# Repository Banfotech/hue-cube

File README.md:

# Introduction 

The HueCube is a small colorful, programmable cube measuring 46x46x46mm.
You can play around with the example code using the [Arduino IDE](https://www.arduino.cc/), and change it's behavior.
By reading data from the embedded sensors, you can let the colors change by temperature, height, angle, tapping, tilting, dropping or humidity. See the following videos for a few examples:

## What do you need?

### Soldering
To assemble the board you need to be able to solder SMD components (0603) and a few pins. I am using [this](https://www.aliexpress.com/item/Hot-Sale-220V-110V-60W-Adjustable-Temperature-Electric-Soldering-Iron-Welding-Solder-Station-Heat-Pencil-With/32434361333.html) and [this](https://www.aliexpress.com/item/Free-Shipping-0-3mm-0-4mm-0-5-mm0-6mm-Tin-Lead-Rosin-Core-Solder-Wire/32335236726.html).

### Software
- [Blender3D](https://www.blender.org/), to design the 3d printed case:
    * USB Powered: <br/>
    * LiPo Powered:<br/>
- [KiCad](http://kicad-pcb.org/), to design the PCB
    * Schematics: <br/>
    * Circuit Board: <br/>
- [Arduino IDE](https://www.arduino.cc/), to write the code and flash the device
   * <br/>
   * The [light_ws2812](https://github.com/cpldcpu/light_ws2812) library to control the LEDs. Download the .zip from the `/light_ws2812_Arduino/` folder and place it into `Arduino/libraries/`. I chose this library, due to the small flash size of the attiny85.

### Hardware
The HueCube is made of small, electronic modules that are soldered onto a PCB. You can order the PCB directly from [AISLER](https://aisler.net/p/VAADXKWB), or use the [KiCad](http://kicad-pcb.org/) project files form this repository to modify it.
Currently, there are two design variant.

- USB Powered
    * 3D printed parts: 1x `BlenderModel/hc-v3-usb-base.stl` and  1x `BlenderModel/hc-v3-usb-cube.stl`
    * [1x ATTiny / DigiSpark](https://www.aliexpress.com/item/Attiny85-Digispark-Kickstarter-Development-Board-Module-For-Arduino-Built-in-USB-500ma-5V-Regulator-8k-Flash/32279051124.html)
    * [1x MPU-6050](https://www.aliexpress.com/item/MPU-6050-3-Axis-gyroscope-acce-lerometer-module-3V-5V-compatible-For-Arduino/2035920870.html)
    * [1x ON/OFF Switch](https://www.aliexpress.com/item/Promotion-50-Pcs-SS12D00G3-2-Position-SPDT-1P2T-3-Pin-PCB-Panel-Mini-Vertical-Slide-Switch/32649542037.html) (I know, not the ideal switch, but I had those lying around, so I will be using them)
    * [3x WS2812B](https://www.aliexpress.com/item/100PCS-New-Version-WS2812B-5050-RGB-SMD-WS2811-IC-WS2812-For-Strip-Screen-etc/32776703442.html) you can use them for all sorts of projects ;)
    * [3x 0603 100nF Capacitor](https://www.aliexpress.com/item/MCIGICM-100pcs-0603-smd-capacitor-ceramic-22pf-100nf-1uf-2-2uf-4-7uf-10uf-capacitors-kit/32841971485.html) (or you could search for a kit with multiple values)
- LiPo Powered
    * 3D printer files: 1x `BlenderModel/hc-v3-lipo-base.stl` and 1x `BlenderModel/hc-v3-lipo-cube.stl`
    * [1x TP4056 LiPo Charger](https://www.aliexpress.com/item/5Pcs-Lot-TP4056-Micro-USB-5V-1A-18650-Lithium-Battery-Charger-Board-With-Led-Indicator-Over/32675099957.html) **⚠️make sure to replace the PROG resistor⚠️**. The resistor value depends on your LiPo size. When using a 400mA battery, use [1x 10k Ohm 0603](https://www.aliexpress.com/item/300pcs-0603-SMD-Resistor-1-6-8K-7-5K-8-2K-9-1K-10K-ohm/32308220603.html?spm=a2g0s.9042311.0.0.27424c4dsotU5N), this will give you around ~100mA charging current. (or you could search for a kit with multiple values)
    * [1x MT3608 DC-DC Step Up Converter](https://www.aliexpress.com/item/5pcs-MT3608-DC-DC-Step-Up-Power-Apply-Module-Booster-Power-Module-MAX-output-28V-2A/32517710689.html) **⚠️set this to 5V output before soldering⚠️**

## How to Build?

### Soldering

#### Manually soldering the LEDs
First, solder the WS2812B to the PCB, note the corner with the triangle is GND, so this needs to be aligned to the bottom right pad. See the video for detais:

*Video:*

#### SMD soldering the LEDs
If you have a hot airstation and liquid solder, it is a lot easier to solder the SMD components:

*Video:*

#### Pins
After the LEDs and capacitors, you will need to solder the pins. 
**Important:** You need to know in advance if you want to build the LiPo version or not, otherwise you will not be able to add the respective pins for the DCDC booster and the LiPo charger module.

*Video:*

#### Sensor + DigiSpark (USB Version)
The USB version only requires soldering the top parts

*Video:*

#### DCDC Booster + LiPo Charger
Note, make sure you have the pins in place. Set the DCDC booster to 5V **before soldering** and **replace the PROG resistor** with a 10k resistor to make sure you only have small charging current of about 120mA.

*Video:*

#### Switch and Battery Connector
I think you will figure these out on your own. The square pin hole (PCB rev.8) is GND (black cable), the other 3.7V (red cable). Solder the connector facing to the bottom, i.e. not on the side of the LEDs.
The switch selects whether the LiPo charger is connected (=OFF or Charging) or the DCDC booster is conencted (=ON). **Never connect the USB while the huecube is on**. I have done it and nothing happened. But it is not designed to work this way.

### 3D Printing
TODO 😅

### Programming
TODO

## License

See the respective subfolders for their LICENSE.

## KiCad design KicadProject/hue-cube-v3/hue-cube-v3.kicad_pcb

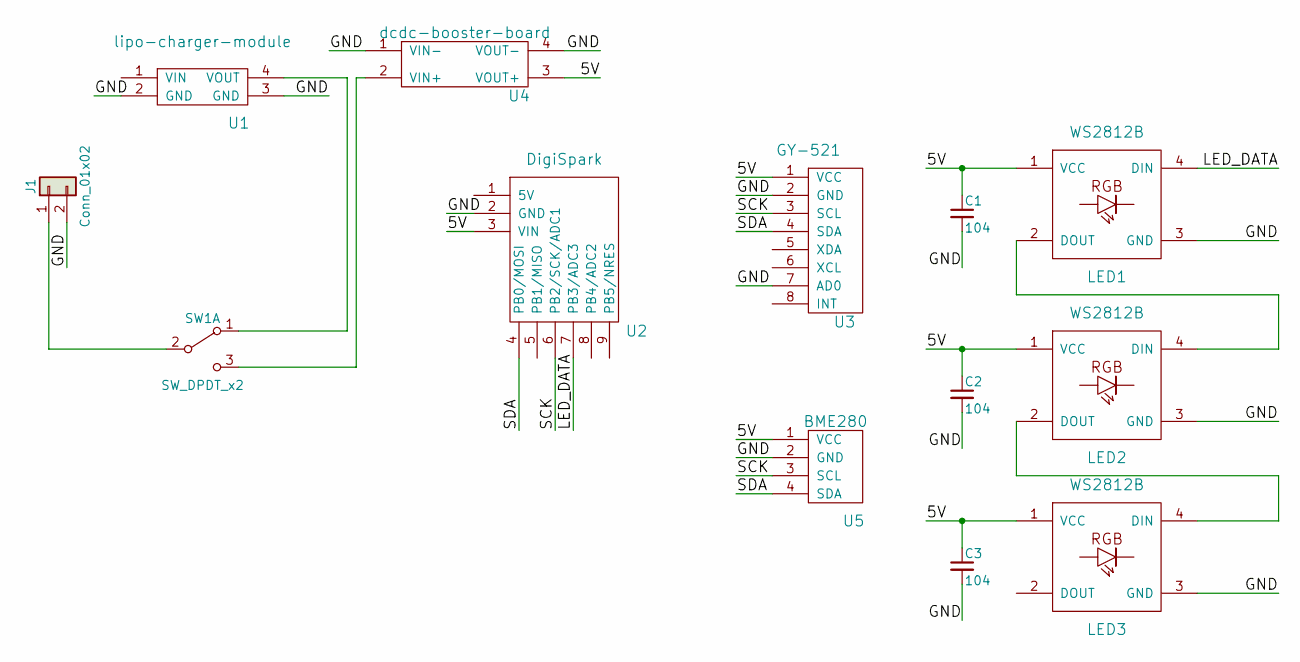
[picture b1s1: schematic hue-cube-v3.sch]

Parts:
C1, C2, C3: 104; C_0603_HandSoldering_narrow
J1: Conn_01x02; JST_XH_B02B-XH-A_02x2.50mm_Straight
LED1, LED2, LED3: WS2812B; WS2812B_data-bridgeable
SW1: SW_DPDT_x2; flat-switch-2.54mm-smd
U1: lipo-charger-module; lipo-charger-board
U2: DigiSpark
U3: GY-521
U4: dcdc-booster-board
U5: BME280

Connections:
/5V: C1.1, C2.1, C3.1, LED1.1 (VCC), LED2.1 (VCC), LED3.1 (VCC), U2.3 (VIN), U3.1 (VCC), U4.3 (VOUT+), U5.1 (VCC)
/GND: C1.2, C2.2, C3.2, J1.2, LED1.3 (GND), LED2.3 (GND), LED3.3 (GND), U1.2 (GND), U1.3 (GND), U2.2 (GND), U3.2 (GND), U3.7 (AD0), U4.1 (VIN-), U4.4 (VOUT-), U5.2 (GND)
/LED_DATA: LED1.4 (DIN), U2.7 (PB3/ADC3)
/SCK: U2.6 (PB2/SCK/ADC1), U3.3 (SCL), U5.3 (SCL)
/SDA: U2.4 (PB0/MOSI), U3.4 (SDA), U5.4 (SDA)
unnamed: J1.1, SW1.2 (B)
unnamed: LED1.2 (DOUT), LED2.4 (DIN)
unnamed: LED2.2 (DOUT), LED3.4 (DIN)
unnamed: SW1.1 (A), U1.4 (VOUT)
unnamed: SW1.3 (C), U4.2 (VIN+)

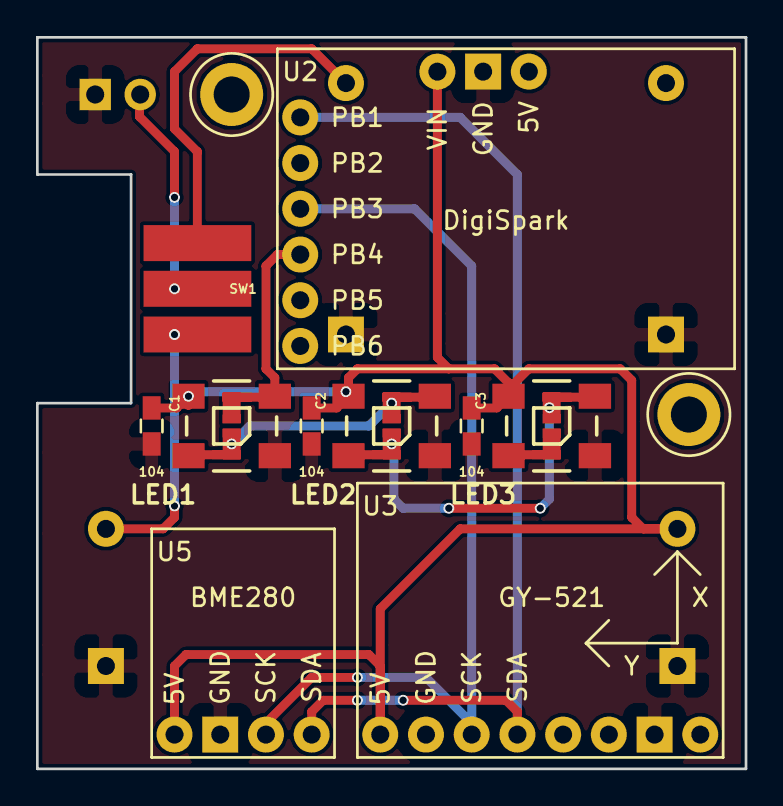
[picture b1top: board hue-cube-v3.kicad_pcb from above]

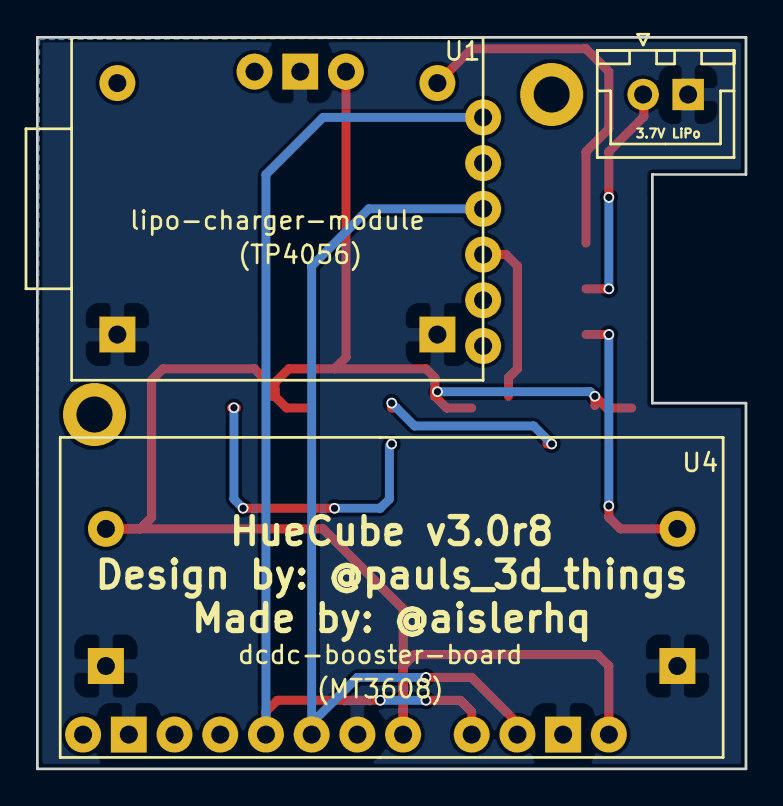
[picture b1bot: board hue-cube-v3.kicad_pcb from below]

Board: 2 copper layers, 39.4 x 40.6 mm, 13 parts (3 on the bottom side), 10 nets.

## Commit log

2018-08-01 Add info about LEDs and DCDC converter
2018-08-01 Add more info on light_ws2812b
2018-09-22 Add switchable tilte+fire mode
